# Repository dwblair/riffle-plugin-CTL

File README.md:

riffle-CTL
==========

External module for riffle datalogger that measures conductivity, temperature, and light levels

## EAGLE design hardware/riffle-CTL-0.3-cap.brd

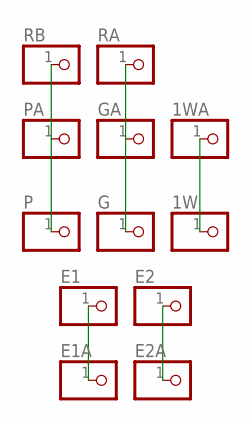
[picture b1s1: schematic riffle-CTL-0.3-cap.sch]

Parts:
1W, 1WA: PINHD-1X1; 1X01
E1, E1A, E2, E2A: PINHD-1X1; 1X01
G: PINHD-1X1; 1X01
GA: PINHD-1X1; 1X01
P: PINHD-1X1; 1X01
PA: PINHD-1X1; 1X01
RA: PINHD-1X1; 1X01
RB: PINHD-1X1; 1X01

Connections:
unnamed: P.1, PA.1, RB.1
unnamed: G.1, GA.1, RA.1
unnamed: 1W.1, 1WA.1
unnamed: E1.1, E1A.1
unnamed: E2.1, E2A.1

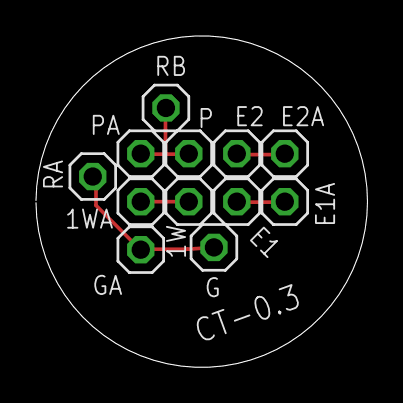
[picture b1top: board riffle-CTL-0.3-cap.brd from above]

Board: 2 copper layers, 18.4 x 18.4 mm, 12 parts (0 on the bottom side), 5 nets.

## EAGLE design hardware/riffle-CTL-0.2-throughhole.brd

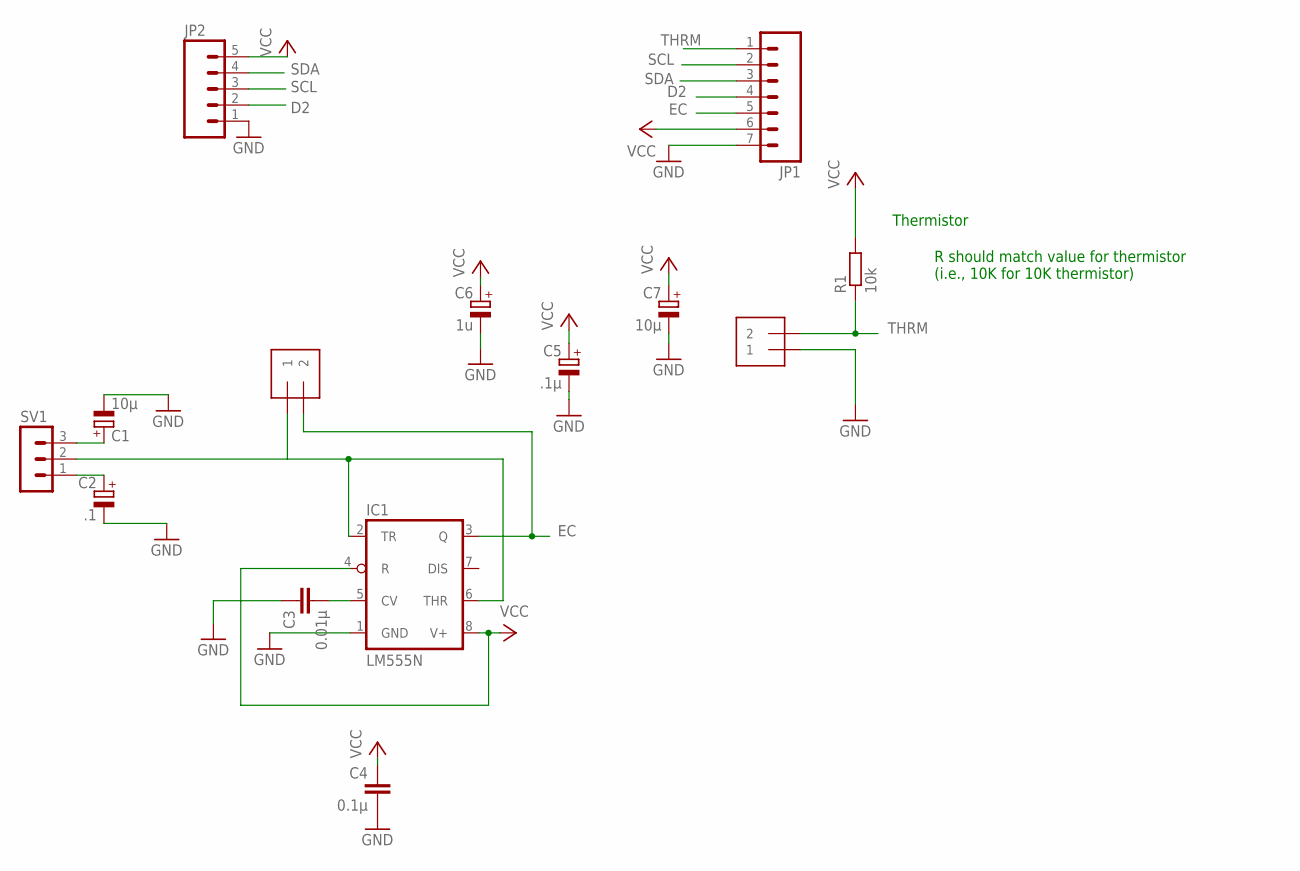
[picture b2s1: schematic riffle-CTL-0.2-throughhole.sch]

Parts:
C1, C7: 10µ; E1,8-4
C2: .1; E1,8-4
C3: 0.01µ; C025-024X044
C4: 0.1µ; C025-024X044
C5: .1µ; E1,8-4
C6: 1u; E1,8-4
EC1: 1X2-3.5MM
IC1: LM555N; DIL08
JP1: M07; 1X07
JP2: M05PTH; 1X05
R1: 10k; 0204/7
SV1: MA03-1
THRM: 1X2-3.5MM

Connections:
D2: JP1.4, JP2.2
EC: EC1.2, IC1.3 (Q), JP1.5
GND: C1.-, C2.-, C3.1, C4.2, C5.-, C6.-, C7.-, IC1.1 (GND), JP1.7, JP2.1, THRM.1
unnamed: C1.+, SV1.3
unnamed: EC1.1, IC1.2 (TR), IC1.6 (THR), SV1.2
unnamed: C2.+, SV1.1
unnamed: C3.2, IC1.5 (CV)
SCL: JP1.2, JP2.3
SDA: JP1.3, JP2.4
THRM: JP1.1, R1.1, THRM.2
VCC: C4.1, C5.+, C6.+, C7.+, IC1.4 (R), IC1.8 (V+), JP1.6, JP2.5, R1.2

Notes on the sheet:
Thermistor
R should match value for thermistor (i.e., 10K for 10K thermistor)

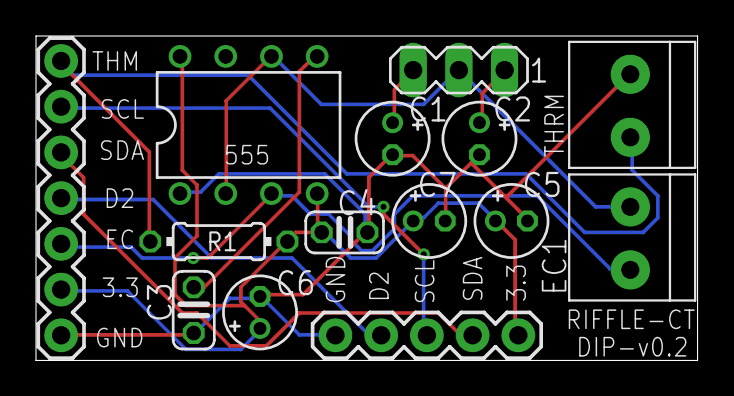
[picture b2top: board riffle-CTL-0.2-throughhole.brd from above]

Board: 2 copper layers, 36.8 x 18.0 mm, 14 parts (0 on the bottom side), 11 nets.

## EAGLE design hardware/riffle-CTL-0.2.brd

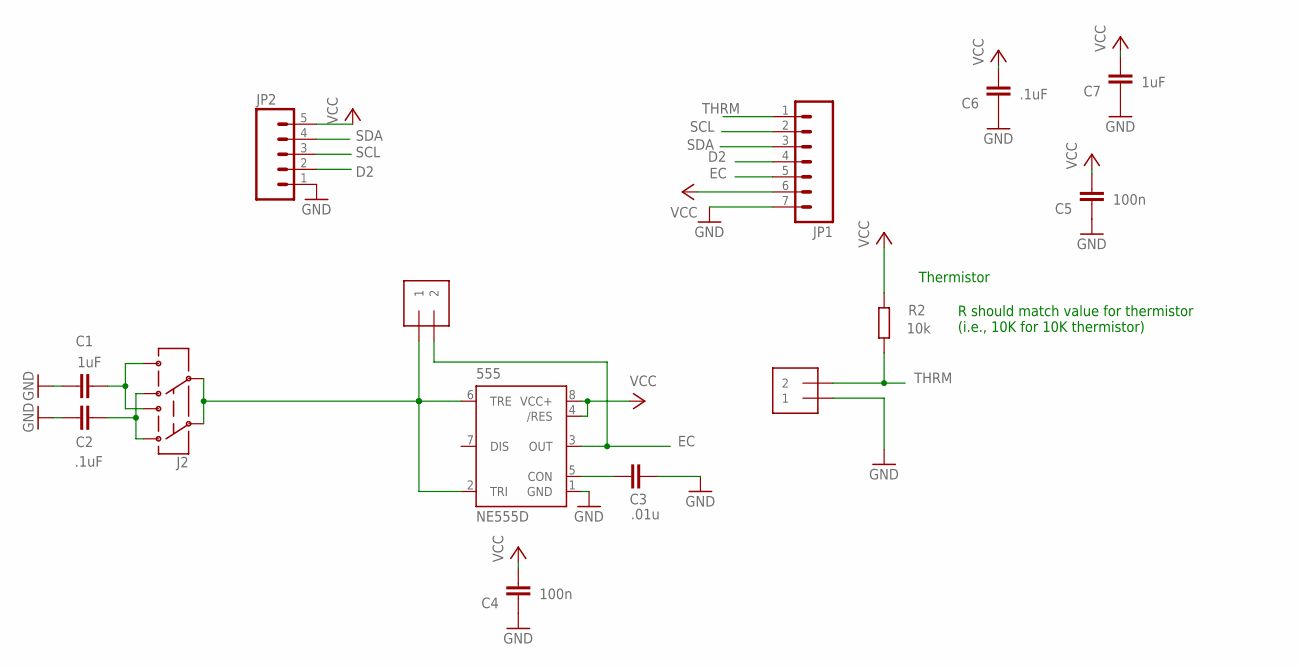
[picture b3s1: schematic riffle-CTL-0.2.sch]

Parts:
555: NE555D; SO08@1
C1, C7: 1uF; C0805
C2, C6: .1uF; C0805
C3: .01u; C0805
C4, C5: 100n; C0805
EC: 1X2-3.5MM
J2: AYZ0202
JP1: M07; 1X07
JP2: M05PTH; 1X05
R2: 10k; R0805
THRM: 1X2-3.5MM

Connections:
D2: JP1.4, JP2.2
EC: 555.3 (OUT), EC.2, JP1.5
GND: 555.1 (GND), C1.2, C2.2, C3.1, C4.1, C5.1, C6.1, C7.1, JP1.7, JP2.1, THRM.1
N1: 555.2 (TRI), 555.6 (TRE), EC.1, J2.2, J2.5
unnamed: 555.5 (CON), C3.2
unnamed: C2.1, J2.3 (1), J2.6 (4)
SCL: JP1.2, JP2.3
SDA: JP1.3, JP2.4
THRM: JP1.1, R2.1, THRM.2
VCC: 555.4 (/RES), 555.8 (VCC+), C4.2, C5.2, C6.2, C7.2, JP1.6, JP2.5, R2.2
VDD2: C1.1, J2.1 (3), J2.4 (6)

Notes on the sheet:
Thermistor
R should match value for thermistor (i.e., 10K for 10K thermistor)

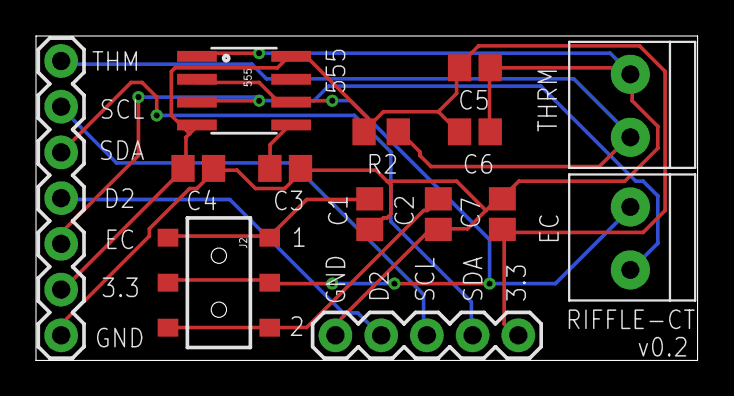
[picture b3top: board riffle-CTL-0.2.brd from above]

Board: 2 copper layers, 36.8 x 18.0 mm, 14 parts (0 on the bottom side), 11 nets.

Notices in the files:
hardware/riffle-CTL-0.2-throughhole.brd:
CERN OHL v1.2
parts and their libraries:
SparkFun-Connectors: Licensing: Creative Commons ShareAlike 4.0 International - https://creativecommons.org/licenses/by-sa/4.0
